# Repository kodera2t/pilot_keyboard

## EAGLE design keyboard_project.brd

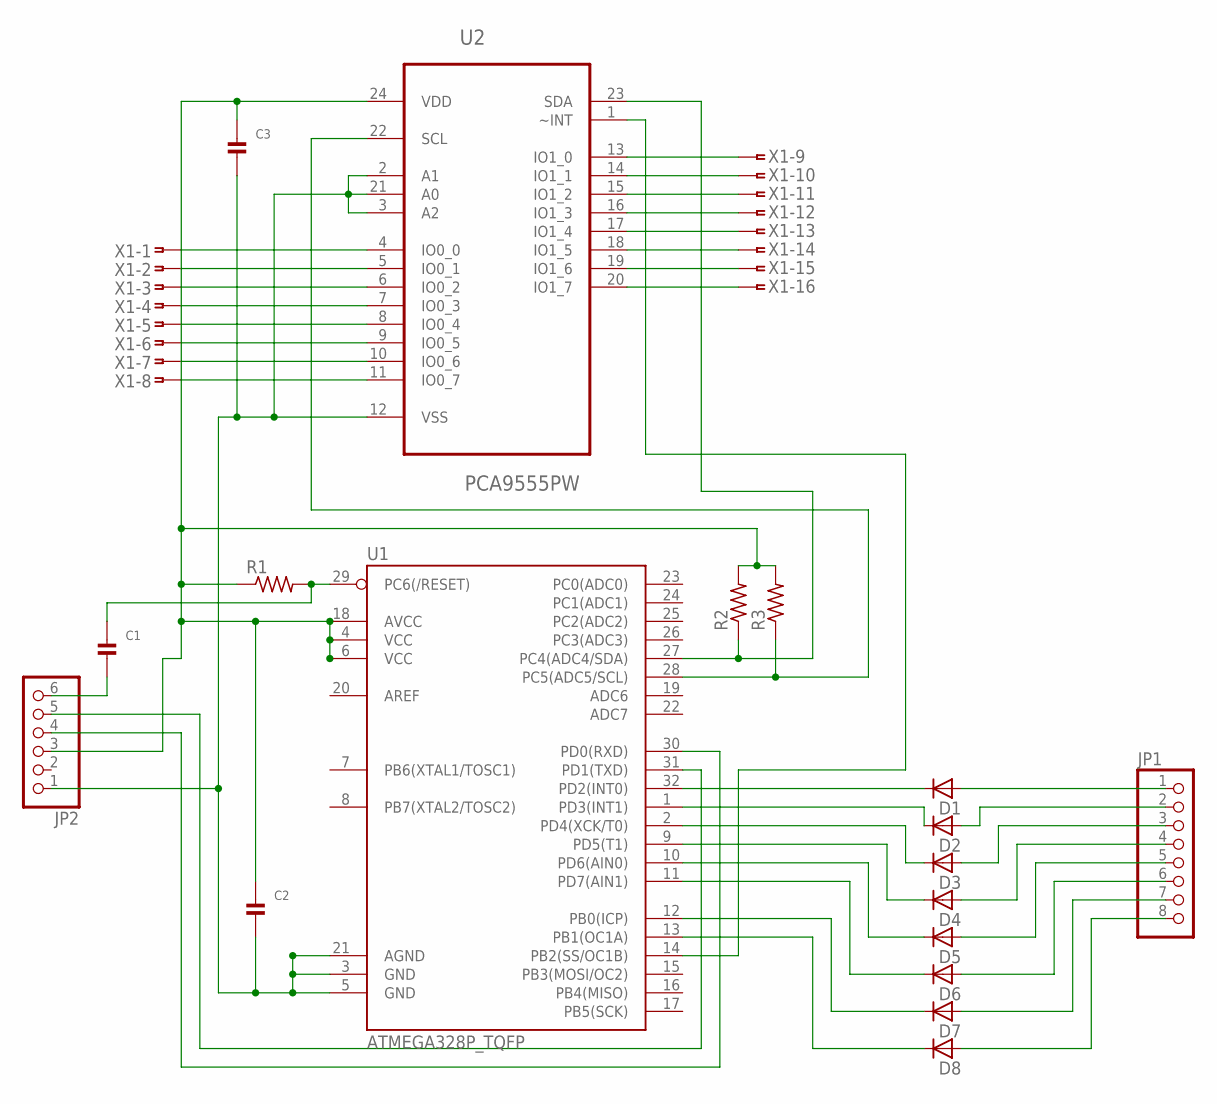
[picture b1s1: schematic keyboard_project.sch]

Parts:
C1, C2, C3: CAP_CERAMIC0603; 0603
D1, D2, D3, D4, D5, D6, D7, D8: D1N4148; D45/2
JP1: PINHD-1X8; 1X08
JP2: HEADER-1X6; 1X06_OVAL
R1, R2, R3: R-US_R0603; R0603
U1: ATMEGA328P_TQFP; TQFP32-08
U2: PCA9555PW; SOP65P640X110-24N
X1: FTOP-16

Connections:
unnamed: U2.4 (IO0_0), X1.1
unnamed: U2.5 (IO0_1), X1.2
unnamed: U2.6 (IO0_2), X1.3
unnamed: U2.7 (IO0_3), X1.4
unnamed: U2.8 (IO0_4), X1.5
unnamed: U2.9 (IO0_5), X1.6
unnamed: U2.10 (IO0_6), X1.7
unnamed: U2.11 (IO0_7), X1.8
unnamed: U2.13 (IO1_0), X1.9
unnamed: U2.14 (IO1_1), X1.10
unnamed: U2.15 (IO1_2), X1.11
unnamed: U2.16 (IO1_3), X1.12
unnamed: U2.17 (IO1_4), X1.13
unnamed: U2.18 (IO1_5), X1.14
unnamed: U2.19 (IO1_6), X1.15
unnamed: U2.20 (IO1_7), X1.16
unnamed: D1.A, JP1.1
unnamed: D2.A, JP1.2
unnamed: D3.A, JP1.3
unnamed: D4.A, JP1.4
unnamed: D5.A, JP1.5
unnamed: D6.A, JP1.6
unnamed: D7.A, JP1.7
unnamed: D8.A, JP1.8
unnamed: D1.C, U1.32 (PD2(INT0))
unnamed: D2.C, U1.1 (PD3(INT1))
unnamed: D3.C, U1.2 (PD4(XCK/T0))
unnamed: D4.C, U1.9 (PD5(T1))
unnamed: D5.C, U1.10 (PD6(AIN0))
unnamed: D6.C, U1.11 (PD7(AIN1))
unnamed: D7.C, U1.12 (PB0(ICP))
unnamed: D8.C, U1.13 (PB1(OC1A))
unnamed: R3.1, U1.28 (PC5(ADC5/SCL)), U2.22 (SCL)
unnamed: R2.1, U1.27 (PC4(ADC4/SDA)), U2.23 (SDA)
unnamed: C2.2, C3.2, JP2.1, U1.3 (GND), U1.5 (GND), U1.21 (AGND), U2.2 (A1), U2.3 (A2), U2.12 (VSS), U2.21 (A0)
unnamed: C2.1, C3.1, JP2.3, R1.1, R2.2, R3.2, U1.4 (VCC), U1.6 (VCC), U1.18 (AVCC), U2.24 (VDD)
unnamed: C1.1, R1.2, U1.29 (PC6(/RESET))
unnamed: C1.2, JP2.6
unnamed: JP2.5, U1.31 (PD1(TXD))
unnamed: JP2.4, U1.30 (PD0(RXD))
unnamed: U1.14 (PB2(SS/OC1B)), U2.1 (~INT)

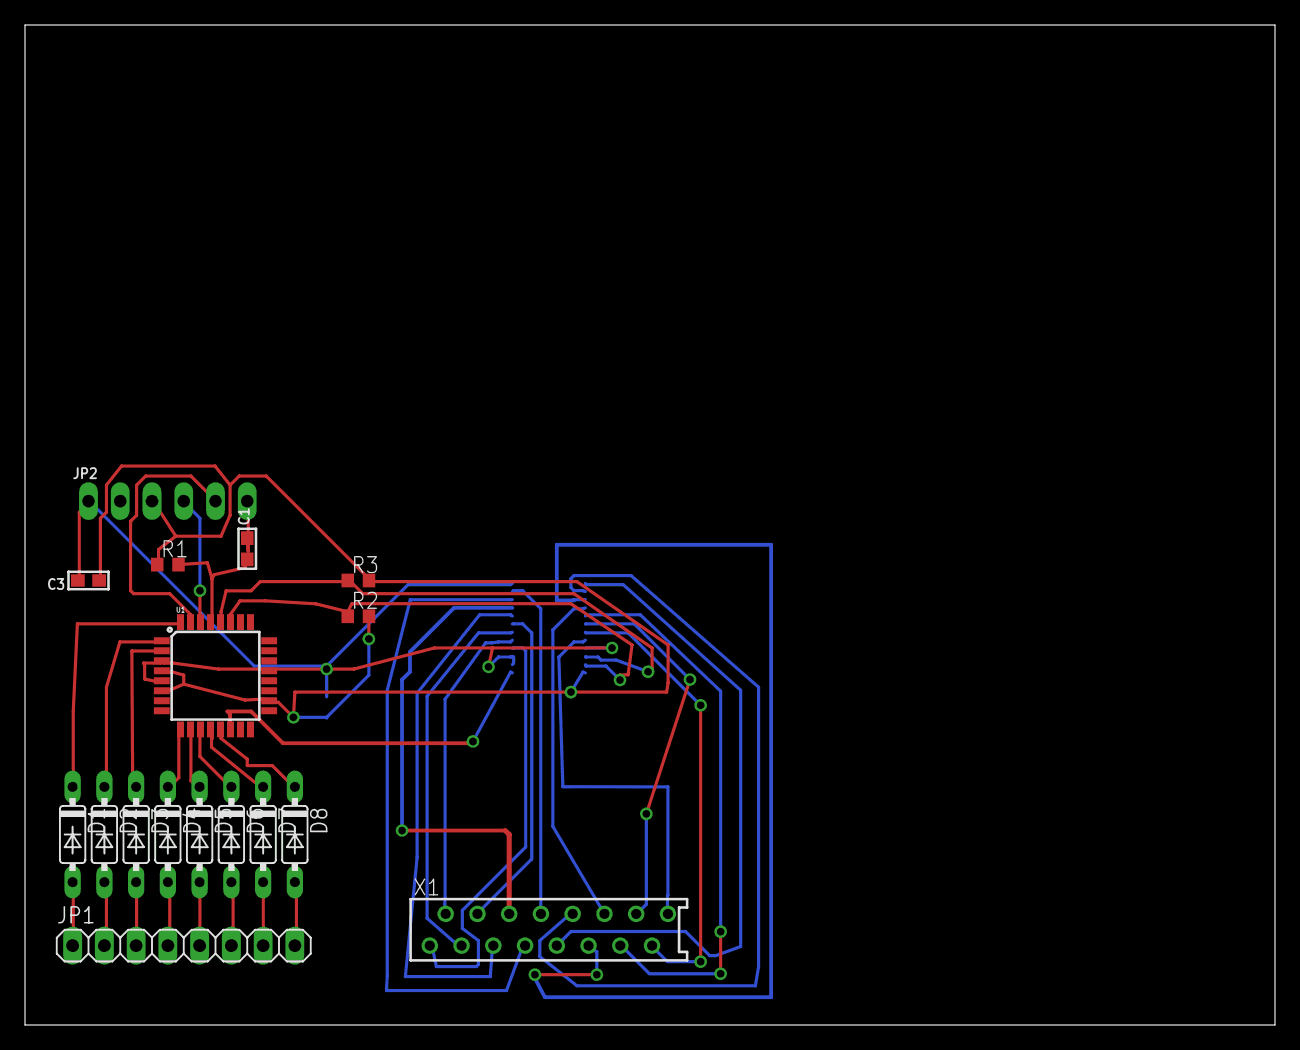
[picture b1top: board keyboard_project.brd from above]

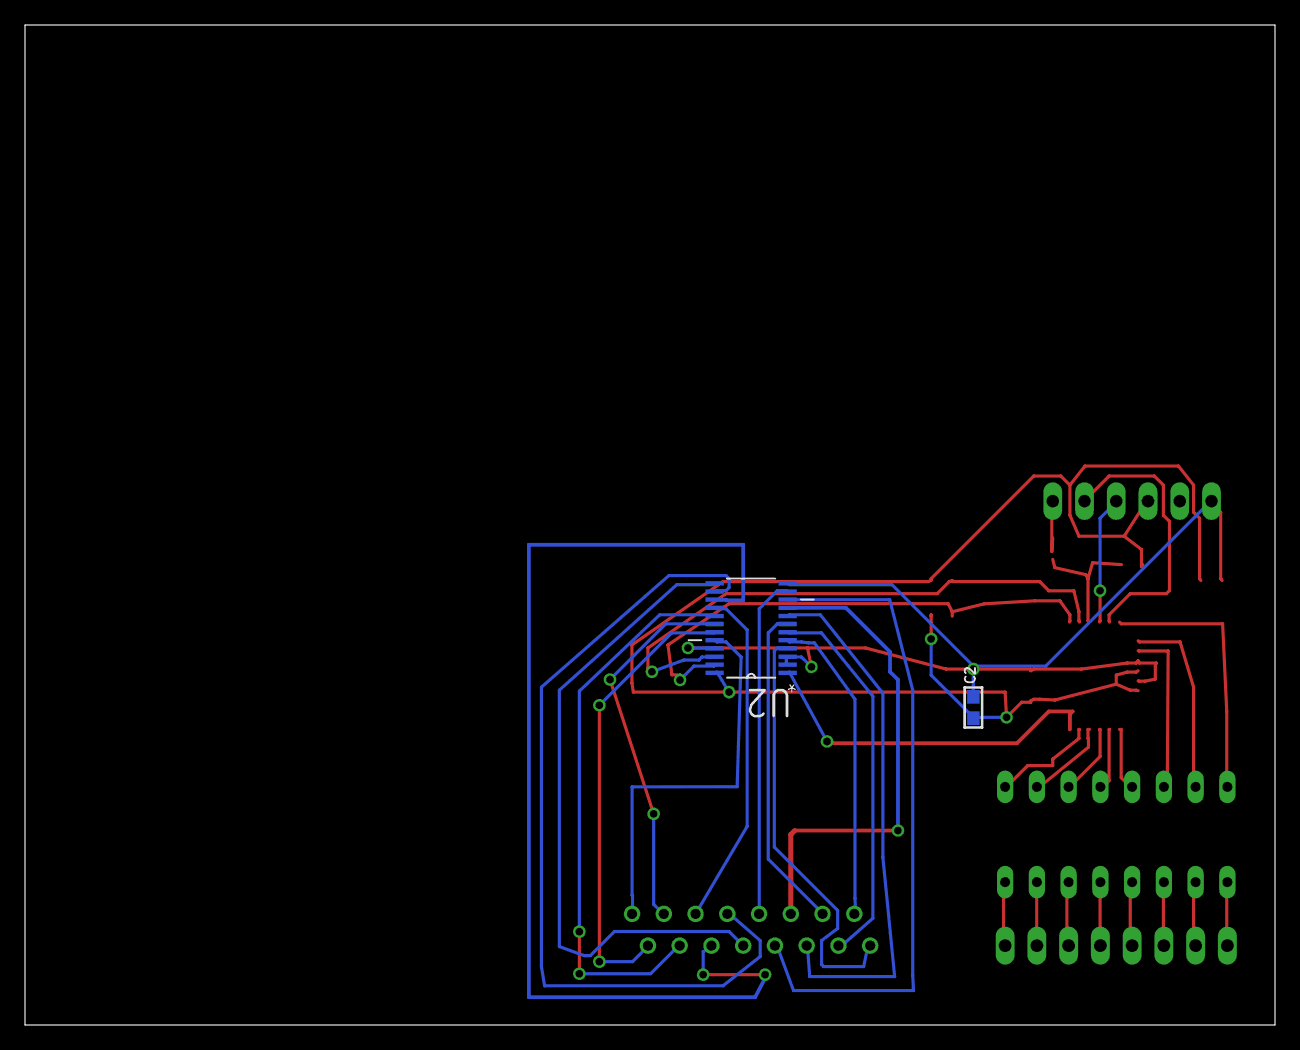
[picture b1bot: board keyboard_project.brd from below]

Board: 2 copper layers, 100.0 x 80.0 mm, 19 parts (2 on the bottom side), 41 nets.

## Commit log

2015-11-03 palm pilot keyboard for tiny computer

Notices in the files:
parts and their libraries:
OLED_mod: This work is placed in the public domain, and may be freely used for commercial and non-commercial work with the following conditions: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
SparkFun-DigitalIC: Licensing: Creative Commons ShareAlike 4.0 International - https://creativecommons.org/licenses/by-sa/4.0
